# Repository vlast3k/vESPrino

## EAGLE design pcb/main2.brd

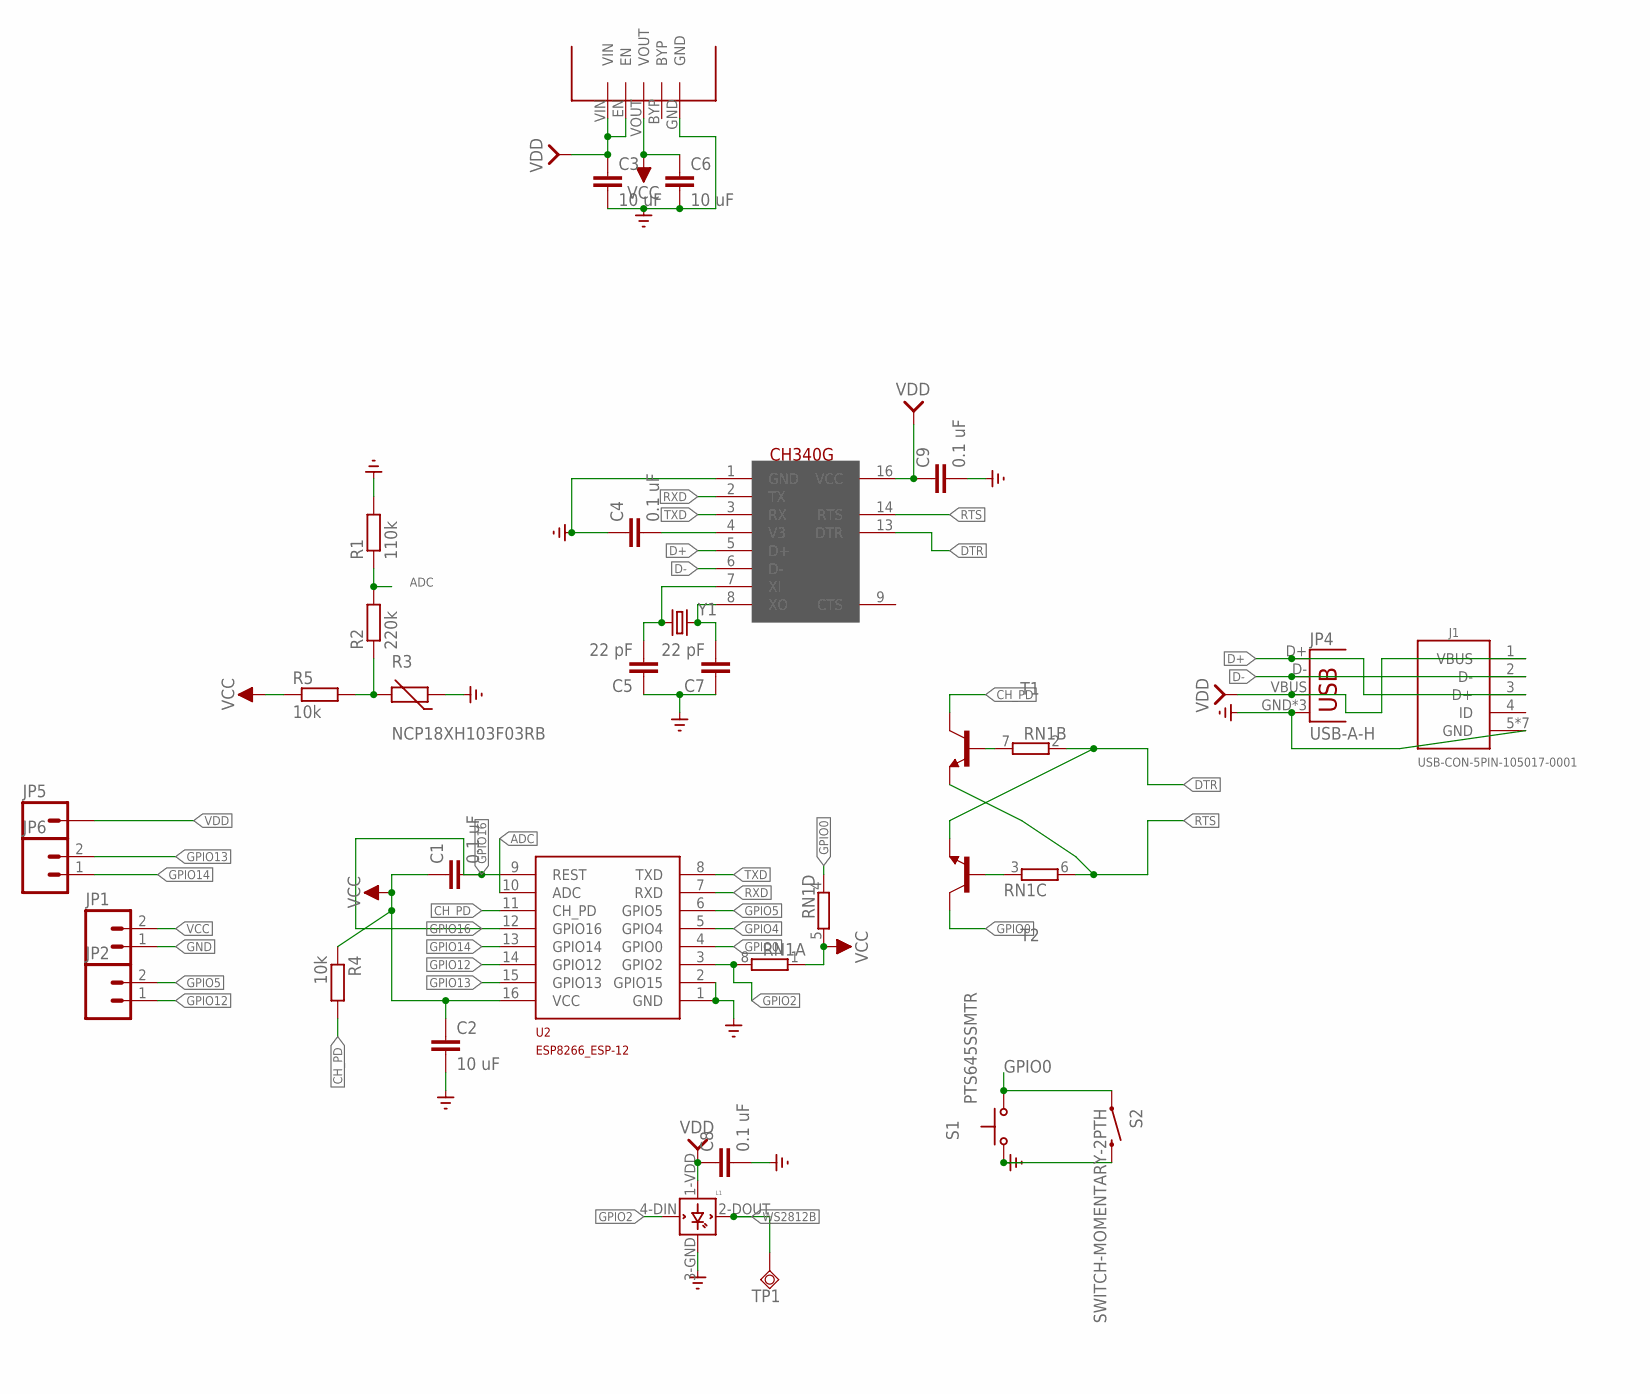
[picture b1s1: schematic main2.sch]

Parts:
C1, C4, C8, C9: 0.1 uF; C0603K
C2, C3, C6: 10 uF; C0603K
C5, C7: 22 pF; C0805K
J1: USB-CON-5PIN-105017-0001; USB-MICRO-MOLEX-105017-0001
JP1, JP2, JP6: M02LOCK; 1X02_LOCK
JP4: USB-A-H
JP5: M01PTH; 1X01
L1: WS2812B
R1: 110k; R0603
R2: 220k; R0603
R3: NCP18XH103F03RB; 0603-RES
R4, R5: 10k; R0805
RN1: 4R-NEXB38V; EXB38V
S1: PTS645SSMTR; PTS645-SMD
S2: SWITCH-MOMENTARY-2PTH; TACTILE-PTH
T1, T2: MMBT2222ALT1-NPN-SOT23-BEC; SOT23-BEC
TP1: TPSQTP20SQ; TP20SQ
U1: SPX3819; SOT23-5L
U2: ESP8266_ESP-12; ESP8266-ESP12
U3: CH340G; SOIC16
Y1: CRYSTALSM49; SM49

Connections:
ADC: R1.1, R2.2, U2.10 (ADC)
CH_PD: R4.2, T1.C, U2.11 (CH_PD)
D+: J1.3 (D+), JP4.D+, U3.5 (D+)
D-: J1.2 (D-), JP4.D-, U3.6 (D-)
DTR: RN1.2 (1), T2.E, U3.13 (DTR)
GND: C2.2, C3.2, C4.1, C5.1, C6.2, C7.1, C8.2, C9.2, J1.5 (GND), J1.P$1 (GND), J1.P$2 (GND), J1.P$3 (GND), J1.P$4 (GND), J1.P$5 (GND), J1.P$6 (GND), JP1.1, JP4.GND, JP4.GND2 (GND), JP4.GND3 (GND), L1.3-GND (GND), R1.2, R3.1, S1.1, S1.2, S2.3 (2), S2.4 (2), U1.GND, U2.1 (GND), U2.2 (GPIO15), U3.1 (GND)
GPIO0: RN1.4 (1), S1.3 (S), S1.4 (S), S2.1, S2.2 (1), T2.C, U2.4 (GPIO0)
GPIO2: L1.4-DIN (DIN), RN1.8 (2), U2.3 (GPIO2)
GPIO4: U2.5 (GPIO4)
GPIO5: JP2.2, U2.6 (GPIO5)
GPIO12: JP2.1, U2.14 (GPIO12)
GPIO13: JP6.2, U2.15 (GPIO13)
GPIO14: JP6.1, U2.13 (GPIO14)
GPIO16: C1.2, U2.9 (REST), U2.12 (GPIO16)
unnamed: C4.2, U3.4 (V3)
unnamed: RN1.3 (1), T2.B
unnamed: RN1.7 (2), T1.B
unnamed: C5.2, U3.7 (XI), Y1.1
unnamed: C7.2, U3.8 (XO), Y1.2
unnamed: R2.1, R3.2, R5.2
RTS: RN1.6 (2), T1.E, U3.14 (RTS)
RXD: U2.7 (RXD), U3.2 (TX)
TXD: U2.8 (TXD), U3.3 (RX)
VCC: C1.1, C2.1, C6.1, JP1.2, R4.1, R5.1, RN1.1, RN1.5 (2), U1.VOUT, U2.16 (VCC)
VDD: C3.1, C8.1, C9.1, J1.1 (VBUS), JP4.VBUS, JP5.1, L1.1-VDD (VDD), U1.EN, U1.VIN, U3.16 (VCC)
WS2812B: L1.2-DOUT (DOUT), TP1.TP

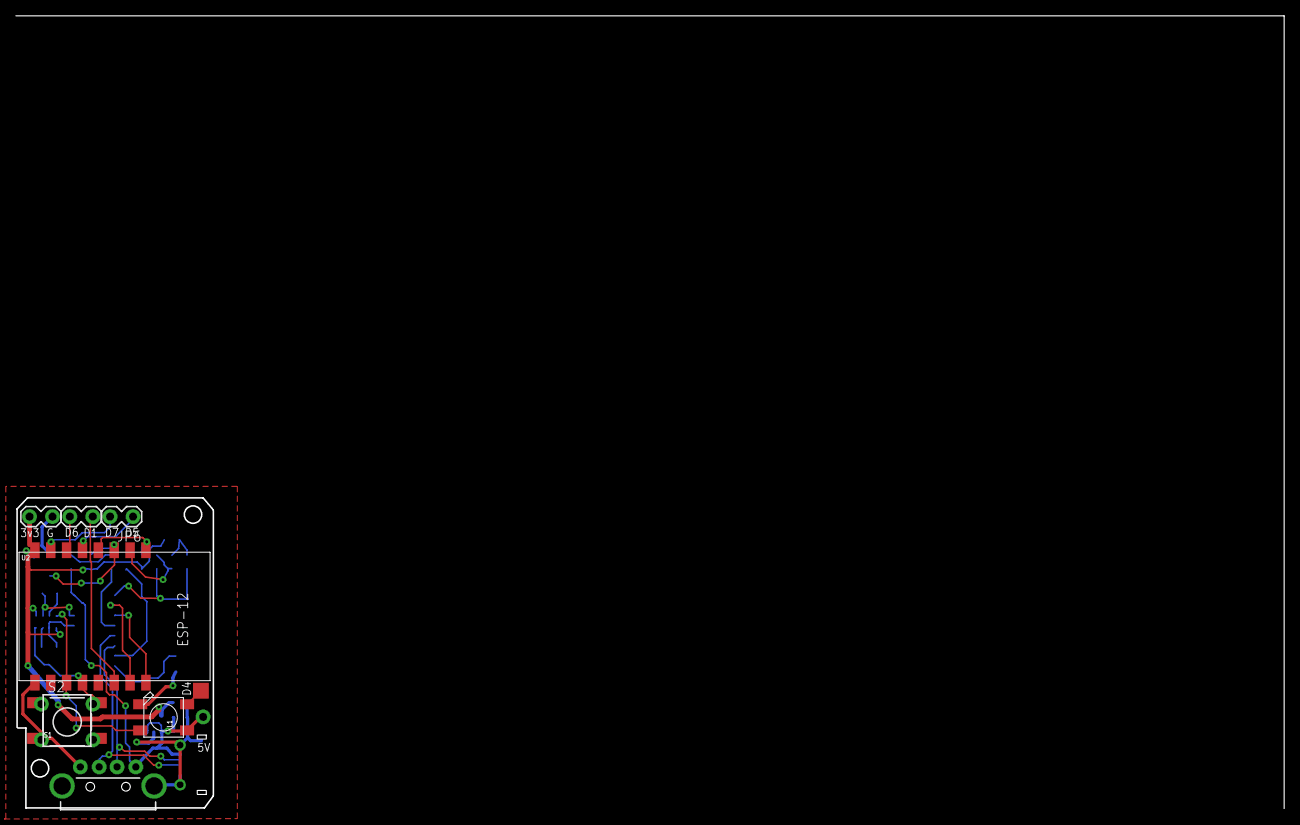
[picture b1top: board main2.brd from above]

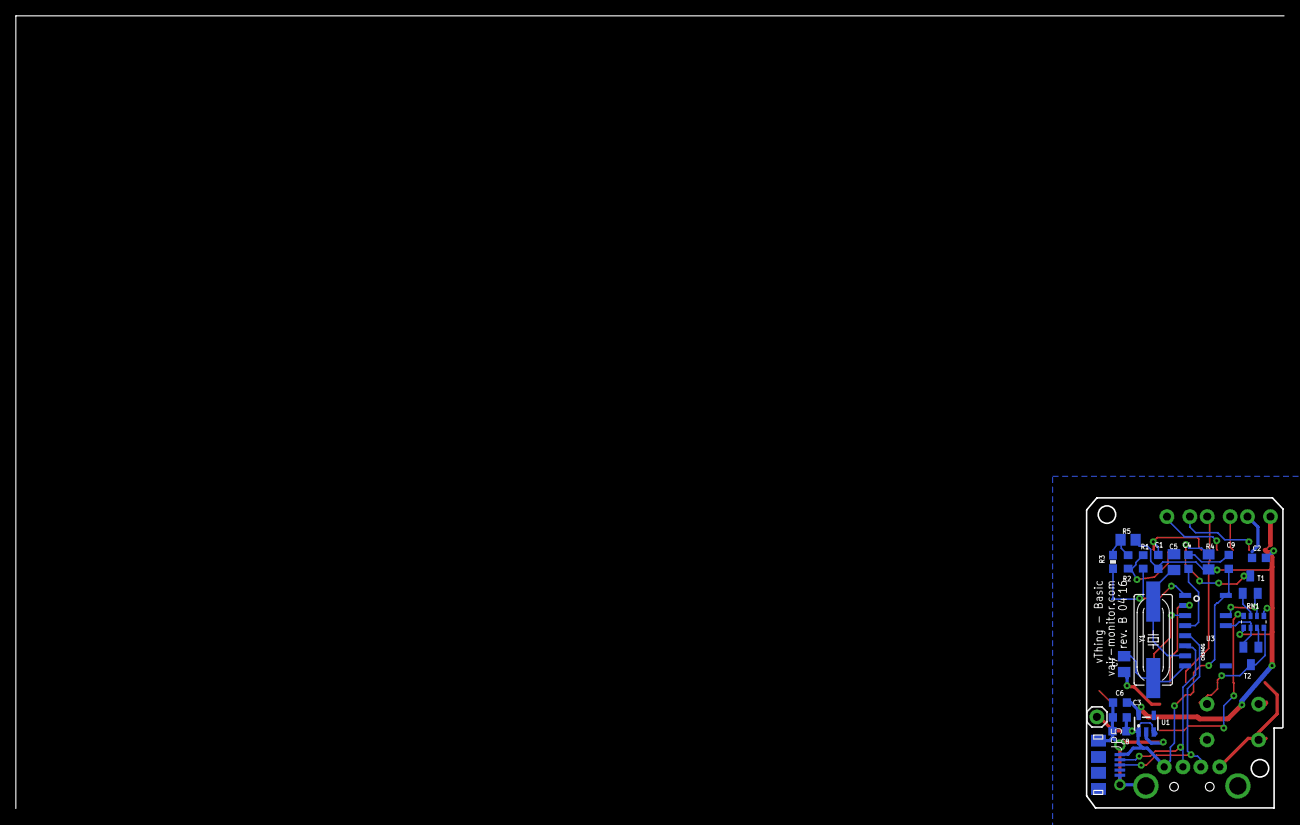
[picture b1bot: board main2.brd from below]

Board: 2 copper layers, 159.8 x 99.8 mm, 31 parts (22 on the bottom side), 25 nets.

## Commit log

2016-06-06 add examples
2016-06-07 Create test
2016-06-07 Submit webpage
2016-06-26 add images and httpserver.js
2016-07-05 https srv
2016-07-11 some img
2016-07-11 ewew
2016-08-01 dasd
2016-08-01 cooklies
2016-11-02 reorder pages
2016-11-15 moved examples
2016-12-26 add support for post

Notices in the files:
parts and their libraries:
SparkFun-Connectors: Licensing: Creative Commons ShareAlike 4.0 International - https://creativecommons.org/licenses/by-sa/4.0
switch-ck: Copyright (C) 2011, Bob Starr
supply4: Copyright (C) 2007, Bob Starr
